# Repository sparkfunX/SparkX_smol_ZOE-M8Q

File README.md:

# SparkX smôl ZOE-M8Q

[*SparkX smôl ZOE-M8Q (SPX-18623)*](https://www.sparkfun.com/products/18623)

The u-blox ZOE-M8Q in smôl format.

## Repository Contents

- **/Documentation** - Datasheets etc.
- **/Hardware** - Eagle design files
- **LICENSE.md** contains the licence information

## Product Versions

- [SPX-18623](https://www.sparkfun.com/products/18623) - Original SparkX Release.

## License Information

This product is _**open source**_!

Please review the LICENSE.md file for license information.

If you have any questions or concerns on licensing, please contact technical support on our [SparkFun forums](https://forum.sparkfun.com/viewforum.php?f=123).

Distributed as-is; no warranty is given.

- Your friends at SparkFun.

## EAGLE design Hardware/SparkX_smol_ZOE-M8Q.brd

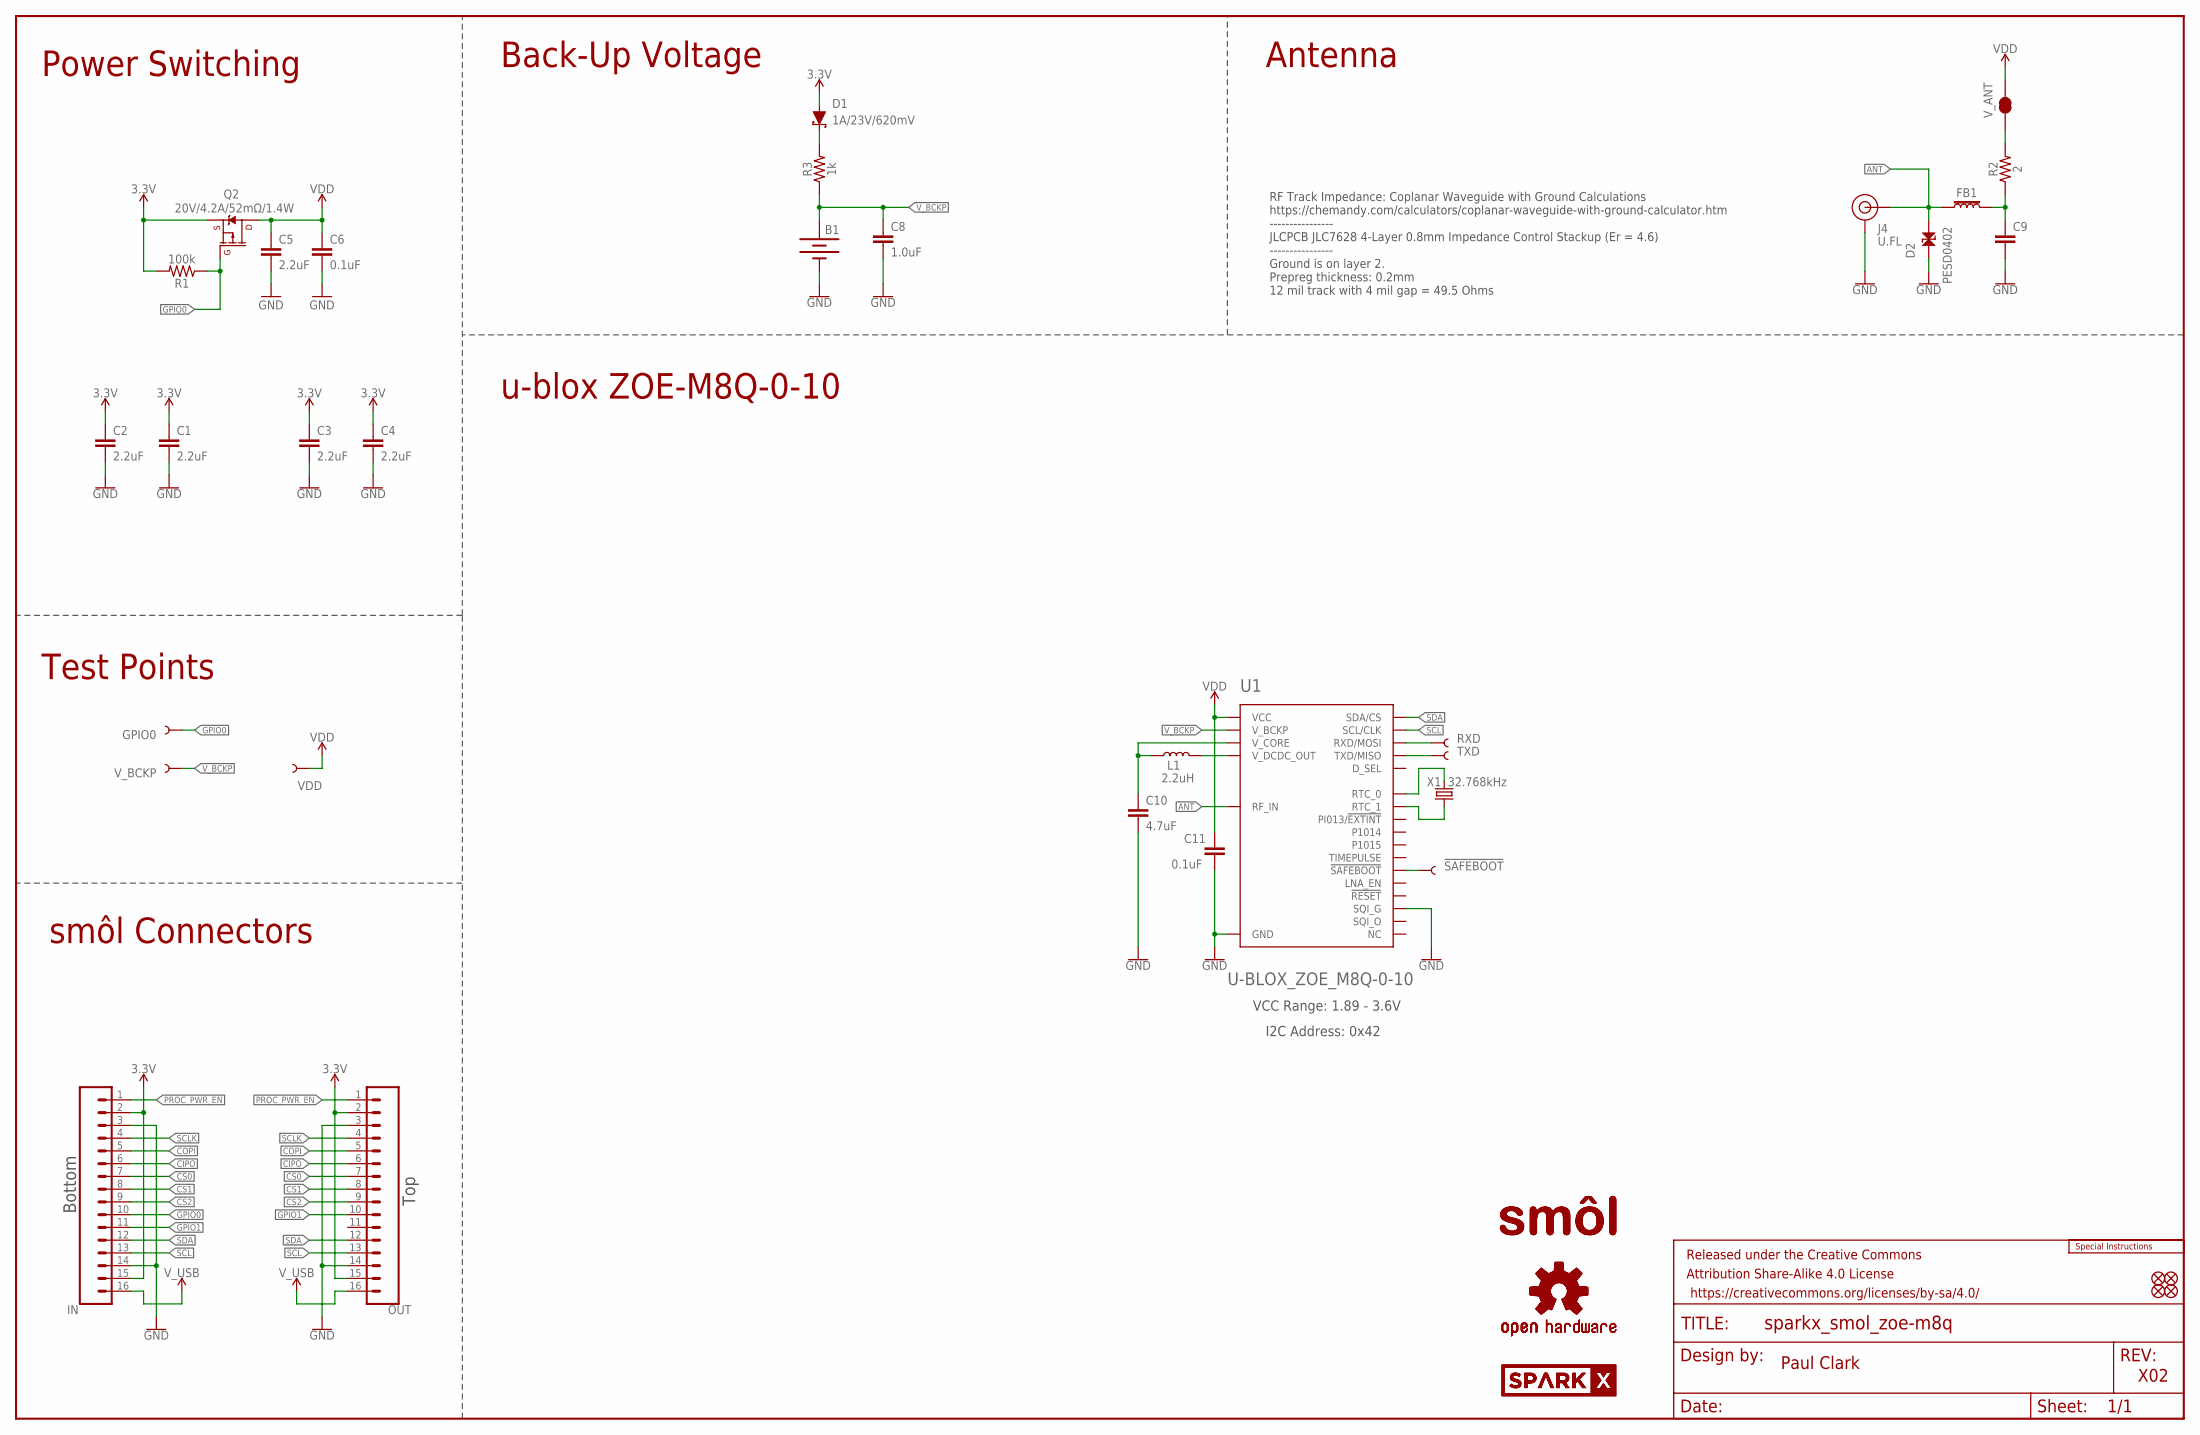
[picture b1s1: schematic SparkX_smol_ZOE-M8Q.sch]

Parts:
!SAFEBOOT!: TEST-POINT3; PAD.03X.03
B1: 6.8MM_COIN_CELL; ML414H_IV01E
C1, C2, C3, C4, C5: 2.2uF; 0402-TIGHT
C6, C11: 0.1uF; 0402-TIGHT
C8: 1.0uF; 0402-TIGHT
C9: 47PF-0402_TIGHT-25V-5%-X7R; 0402-TIGHT
C10: 4.7uF; 0402-TIGHT
D1: 1A/23V/620mV; SOD-323
D2: PESD0402; 0402
FB1: FERRITE_BEAD-120_OHM-0402; 0402
FD1, FD2, FD3, FD4: FIDUCIALUFIDUCIAL; FIDUCIAL-MICRO
FRAME1: FRAME-LEDGER; CREATIVE_COMMONS
GPIO0: TEST-POINT3; PAD.03X.03
IN: CONN_16FPC_16_0.5MM; FPC_16_0.5MM
J4: U.FL
L1: 2.2uH; 0806
LOGO1: SPECIAL_INSTRUCTIONS-ORDERING; ORDERING_INSTRUCTIONS
LOGO2, LOGO3: OSHW-LOGOMINI; OSHW-LOGO-MINI
OUT: CONN_16FPC_16_0.5MM; FPC_16_0.5MM
Q2: 20V/4.2A/52mΩ/1.4W; SOT23-3
R1: 100k; 0402-TIGHT
R2: 2; 0402-TIGHT
R3: 1k; 0402-TIGHT
RXD: TEST-POINT3; PAD.03X.03
TXD: TEST-POINT3; PAD.03X.03
U1: U-BLOX_ZOE_M8Q-0-10; UBLOX_ZOE_M8-0-10
U$1, U$4: SPARKX-LOGO3; SPARKX-SMALL
U$3, U$13: SMOL_LOGOSMALL; SMOL_SMALL
VDD: TEST-POINT3; PAD.03X.03
V_ANT: JUMPER-SMT_2_NC_TRACE_SILK; SMT-JUMPER_2_NC_TRACE_SILK
V_BCKP: TEST-POINT3; PAD.03X.03
X1: 32.768kHz; CRYSTAL-SMD-3.2X1.5MM

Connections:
3.3V: C1.1, C2.1, C3.1, C4.1, D1.A, IN.2, IN.15, OUT.2, OUT.15, Q2.2 (S), R1.2
!SAFEBOOT!: !SAFEBOOT!.1, U1.34 (!SAFEBOOT)
ANT: D2.2, FB1.1, J4.FEED (SIGNAL), U1.4 (RF_IN)
CIPO: IN.6, OUT.6
COPI: IN.5, OUT.5
CS0: IN.7, OUT.7
CS1: IN.8, OUT.8
CS2: IN.9, OUT.9
GND: B1.-, C1.2, C2.2, C3.2, C4.2, C5.2, C6.2, C8.2, C9.2, C10.2, C11.2, D2.1, IN.3, IN.14, J4.1 (GND), J4.2 (GND), OUT.3, OUT.14, U1.1 (GND), U1.3 (GND), U1.5 (GND), U1.7 (GND), U1.8 (GND), U1.9 (GND), U1.10 (GND), U1.11 (GND), U1.12 (GND), U1.17 (GND), U1.23 (GND), U1.29 (SQI_G), U1.31 (SQI_G), U1.37 (GND), U1.38 (GND), U1.39 (GND), U1.40 (GND), U1.41 (GND), U1.44 (GND), U1.46 (SQI_G), U1.47 (SQI_G), U1.49 (GND)
GPIO0: GPIO0.1, IN.10, Q2.1 (G), R1.1
GPIO1: IN.11, OUT.10
unnamed: R2.2, V_ANT.1
unnamed: D1.C, R3.2
unnamed: L1.2, U1.26 (V_DCDC_OUT)
unnamed: C10.1, L1.1, U1.27 (V_CORE)
unnamed: U1.18 (RTC_0), X1.P$2 (2)
unnamed: U1.19 (RTC_1), X1.P$1 (1)
unnamed: C9.1, FB1.2, R2.1
PROC_PWR_EN: IN.1, OUT.1
RXD: RXD.1, U1.22 (RXD/MOSI)
SCL: IN.13, OUT.13, U1.32 (SCL/CLK)
SCLK: IN.4, OUT.4
SDA: IN.12, OUT.12, U1.2 (SDA/CS)
TXD: TXD.1, U1.21 (TXD/MISO)
VDD: C5.1, C6.1, C11.1, Q2.3 (D), U1.24 (VCC), U1.25 (VCC), VDD.1, V_ANT.2
V_BCKP: B1.+, C8.1, R3.1, U1.16 (V_BCKP), V_BCKP.1
V_USB: IN.16, OUT.16

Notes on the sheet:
Paul Clark
X02
Test Points
RF Track Impedance: Coplanar Waveguide with Ground Calculations https://chemandy.com/calculators/coplanar-waveguide-with-ground-calculator.htm ---------------- JLCPCB JLC7628 4-Layer 0.8mm Impedance Control Stackup (Er = 4.6) ---------------- Ground is on layer 2. Prepreg thickness: 0.2mm 12 mil tr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
Power Switching
smôl Connectors
Bottom
Top
u-blox ZOE-M8Q-0-10
Back-Up Voltage
Antenna
VCC Range: 1.89 - 3.6V
I2C Address: 0x42

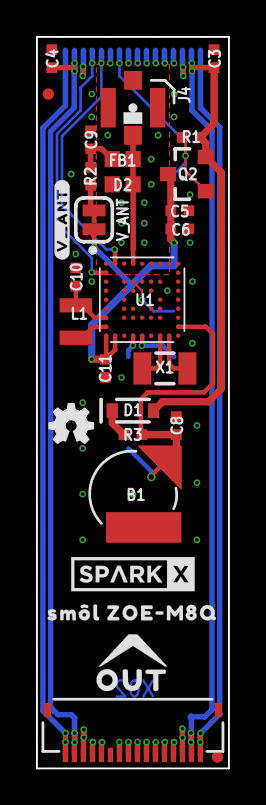
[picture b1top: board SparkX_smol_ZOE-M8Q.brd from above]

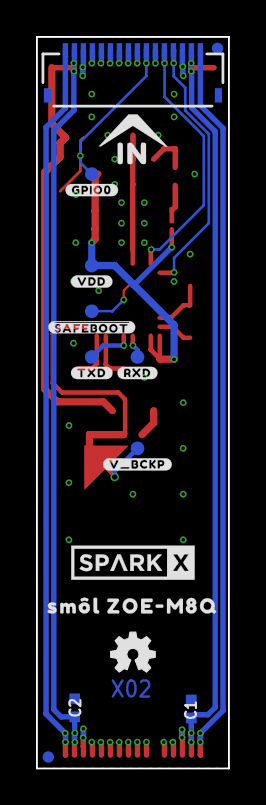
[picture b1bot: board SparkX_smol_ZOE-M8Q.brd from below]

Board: 4 copper layers, 10.7 x 40.6 mm, 54 parts (22 on the bottom side), 27 nets.

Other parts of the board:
U$2, U$12: SM�L_ZOE#M8Q0
U$5: #V_ANT#0
U$6: #VDD#0
U$7: ##SAFEBOOT##0
U$8: #TXD#0
U$9: #RXD#0
U$10: #GPIO0#0
U$11: #V_BCKP#0
U$14: OUT0
U$15: IN0

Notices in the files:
parts and their libraries:
SparkFun-Aesthetics: Licensing: Creative Commons ShareAlike 4.0 International - https://creativecommons.org/licenses/by-sa/4.0
SparkFun-Aesthetics: Released under the Creative Commons Attribution Share-Alike 4.0 License
SparkFun-Aesthetics: https://creativecommons.org/licenses/by-sa/4.0
